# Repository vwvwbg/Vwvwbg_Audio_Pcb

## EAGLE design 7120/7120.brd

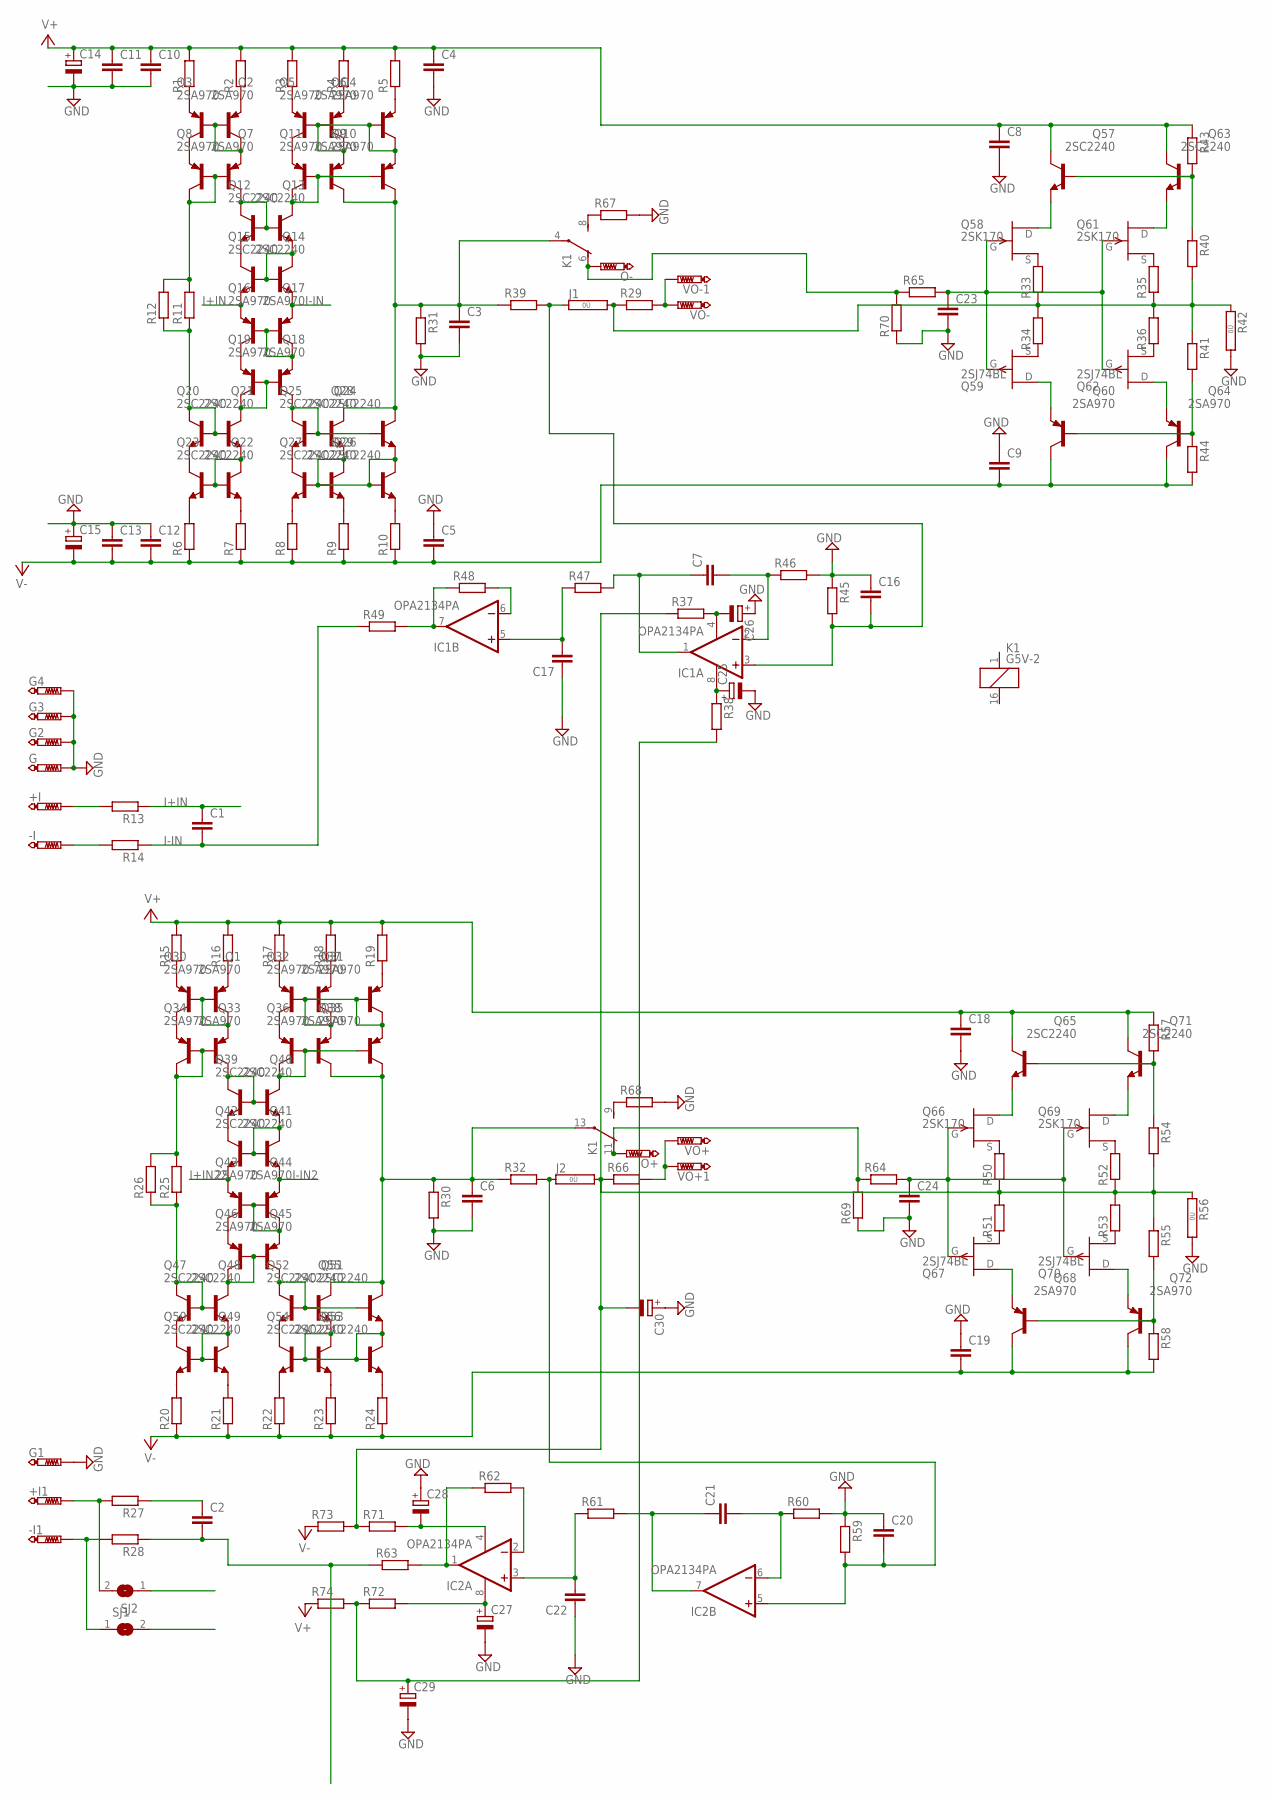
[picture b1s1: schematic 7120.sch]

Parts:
+I, +I1: PTR1PAD1-20; P1-20
-I, -I1: PTR1PAD1-20; P1-20
C1, C2, C7, C17, C21, C22: C-EU050-030X075; C050-030X075
C3, C4, C5, C6, C8, C9, C10, C11, C12, C13, C16, C18, C19, C20, C23, C24: C-EU050-055X075; C050-055X075
C14, C15, C29, C30: CPOL-EUE7.5-18; E7,5-18
C25, C26, C27, C28: CPOL-EUE2.5-6; E2,5-6
G, G1, G2, G3, G4: PTR1PAD1-20; P1-20
IC1, IC2: OPA2134PA; DIL08
J1, J2: 0R; 0R/10
K1: G5V-2
O+: PTR1PAD1-20; P1-20
O-: PTR1PAD1-20; P1-20
Q1, Q2, Q3, Q4, Q5, Q6, Q7, Q8, Q9, Q10, Q11, Q16, Q17, Q18, Q19, Q30, Q31, Q32, Q33, Q34, Q35, Q36, Q37, Q38, Q43, Q44, Q45, Q46, Q60, Q64, Q68, Q72: 2SA970; TO92-BCE
Q12, Q13, Q14, Q15, Q20, Q21, Q22, Q23, Q24, Q25, Q26, Q27, Q28, Q29, Q39, Q40, Q41, Q42, Q47, Q48, Q49, Q50, Q51, Q52, Q53, Q54, Q55, Q56, Q57, Q63, Q65, Q71: 2SC2240; TO92-BCE
Q58, Q61, Q66, Q69: 2SK170; TO92-
Q59, Q62, Q67, Q70: 2SJ74BL; TO92-
R1, R2, R3, R4, R5, R6, R7, R8, R9, R10, R11, R12, R13, R14, R15, R16, R17, R18, R19, R20, R21, R22, R23, R24, R25, R26, R27, R28, R29, R30, R31, R32, R33, R34, R35, R36, R37, R38, R39, R40, R41, R43, R44, R45, R46, R47, R48, R49, R50, R51, R52, R53, R54, R55, R57, R58, R59, R60, R61, R62, R63, R64, R65, R66, R67, R68, R69, R70, R71, R72, R73, R74: R-EU_0207/7; 0207/7
R42, R56: 0R; 0R/10
SJ1, SJ2: SJ
VO+, VO+1: PTR1PAD1-20; P1-20
VO-, VO-1: PTR1PAD1-20; P1-20

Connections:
+I: +I.TP, R13.2, SJ1.2
-I: -I.TP, R14.2, SJ2.1
GND: C3.2, C4.2, C5.1, C6.2, C8.2, C9.1, C10.2, C11.2, C12.1, C13.1, C14.-, C15.+, C16.1, C17.1, C18.2, C19.1, C20.1, C22.1, C23.2, C24.2, C25.-, C26.+, C27.-, C28.+, C29.-, C30.+, G.TP, G1.TP, G2.TP, G3.TP, G4.TP, R30.2, R31.2, R42.2, R45.1, R46.2, R56.2, R59.1, R60.2, R67.2, R68.2, R69.1, R70.1
I+IN: C1.1, Q14.E, Q17.E, R13.1
I+IN2: C2.1, R27.1
I+IN22: Q41.E, Q44.E
I-IN: C1.2, Q15.E, Q16.E, R14.1, R49.1
I-IN1: C2.2, R28.1, R63.1
I-IN2: Q42.E, Q43.E
unnamed: Q2.E, R1.1
unnamed: Q2.B, Q3.B, Q3.C, Q8.E
unnamed: Q3.E, R2.1
unnamed: Q2.C, Q7.E
unnamed: Q7.B, Q7.C, Q8.B, R11.2, R12.2
unnamed: Q4.E, R3.1
unnamed: Q4.B, Q5.B, Q5.C, Q6.B, Q6.C, Q9.E, Q11.E
unnamed: Q5.E, R4.1
unnamed: Q6.E, R5.1
unnamed: Q8.C, Q12.B, Q13.B, Q13.C
unnamed: C3.1, K1.4, Q9.C, Q11.C, Q25.C, Q28.C, R31.1, R39.1
unnamed: Q4.C, Q10.E
unnamed: Q12.E, Q14.B, Q15.B, Q15.C
unnamed: Q9.B, Q10.B, Q10.C, Q11.B, Q12.C
unnamed: C16.2, IC1.3 (+IN), J1.1, R39.2, R45.2
unnamed: Q13.E, Q14.C
unnamed: C6.1, K1.13, Q36.C, Q38.C, Q52.C, Q55.C, R30.1, R32.1
unnamed: Q57.B, Q63.B, R40.1, R43.2
unnamed: Q1.E, R15.1
unnamed: Q16.B, Q16.C, Q17.B, Q19.E
unnamed: Q17.C, Q18.E
unnamed: Q1.B, Q30.B, Q30.C, Q34.E
unnamed: Q18.B, Q18.C, Q19.B, Q20.C
unnamed: Q30.E, R16.1
unnamed: Q20.B, Q21.B, Q21.C, R11.1, R12.1
unnamed: Q21.E, Q22.C
unnamed: Q20.E, Q22.B, Q23.B, Q23.C
unnamed: Q33.B, Q33.C, Q34.B, R25.2, R26.2
unnamed: Q19.C, Q24.B, Q24.C, Q25.B, Q28.B
unnamed: Q1.C, Q33.E
unnamed: Q24.E, Q26.C
unnamed: Q25.E, Q26.B, Q27.B, Q27.C, Q28.E, Q29.B, Q29.C
unnamed: Q31.E, R17.1
unnamed: Q31.B, Q32.B, Q32.C, Q36.E, Q37.B, Q37.C, Q38.E
unnamed: Q32.E, R18.1
unnamed: Q22.E, R6.2
unnamed: Q23.E, R7.2
unnamed: Q26.E, R8.2
unnamed: Q27.E, R9.2
unnamed: Q29.E, R10.2
unnamed: J1.2, R29.1, R33.1, R34.2, R35.1, R36.2, R40.2, R41.1, R42.1
unnamed: Q31.C, Q35.E
unnamed: Q35.B, Q35.C, Q36.B, Q38.B, Q39.C
unnamed: K1.6 (O), O-.TP, R65.1, R70.2
unnamed: Q37.E, R19.1
unnamed: Q60.B, Q64.B, R41.2, R44.1
unnamed: Q34.C, Q39.B, Q40.B, Q40.C
unnamed: Q40.E, Q41.C
unnamed: Q39.E, Q41.B, Q42.B, Q42.C
unnamed: Q43.B, Q43.C, Q44.B, Q46.E
unnamed: Q44.C, Q45.E
unnamed: Q45.B, Q45.C, Q46.B, Q47.C
unnamed: Q47.B, Q48.B, Q48.C, R25.1, R26.1
unnamed: Q48.E, Q49.C
unnamed: Q47.E, Q49.B, Q50.B, Q50.C
unnamed: Q46.C, Q51.B, Q51.C, Q52.B, Q55.B
unnamed: Q51.E, Q53.C
unnamed: Q49.E, R20.2
unnamed: Q50.E, R21.2
unnamed: Q53.E, R22.2
unnamed: Q54.E, R23.2
unnamed: Q56.E, R24.2
unnamed: C7.1, IC1.1 (OUT), R47.2
unnamed: Q52.E, Q53.B, Q54.B, Q54.C, Q55.E, Q56.B, Q56.C
unnamed: +I1.TP, R27.2, SJ2.2
unnamed: -I1.TP, R28.2, SJ1.1
unnamed: Q62.3 (S), R36.1
unnamed: Q59.3 (S), R34.1
unnamed: K1.8 (S), R67.1
unnamed: Q58.3 (S), R33.2
unnamed: Q61.3 (S), R35.2
unnamed: C7.2, IC1.2 (-IN), R46.1
unnamed: C23.1, Q58.2 (G), Q59.2 (G), Q61.2 (G), Q62.2 (G), R65.2
unnamed: Q61.1 (D), Q63.E
unnamed: C17.2, IC1.5 (+IN), R47.1
unnamed: Q57.E, Q58.1 (D)
unnamed: Q62.1 (D), Q64.E
unnamed: Q59.1 (D), Q60.E
unnamed: IC1.7 (OUT), R48.1, R49.2
unnamed: IC1.6 (-IN), R48.2
unnamed: Q65.B, Q71.B, R54.1, R57.2
unnamed: Q68.B, Q72.B, R55.2, R58.1
unnamed: J2.2, R50.1, R51.2, R52.1, R53.2, R54.2, R55.1, R56.1, R66.1
unnamed: C24.1, Q66.2 (G), Q67.2 (G), Q69.2 (G), Q70.2 (G), R64.2
unnamed: Q70.3 (S), R53.1
unnamed: Q67.3 (S), R51.1
unnamed: Q69.1 (D), Q71.E
unnamed: Q70.1 (D), Q72.E
unnamed: Q67.1 (D), Q68.E
unnamed: Q69.3 (S), R52.2
unnamed: Q66.3 (S), R50.2
unnamed: Q65.E, Q66.1 (D)
unnamed: C21.1, IC2.7 (OUT), R61.2
unnamed: C21.2, IC2.6 (-IN), R60.1
unnamed: C20.2, IC2.5 (+IN), J2.1, R32.2, R59.2
unnamed: K1.9 (S), R68.1
unnamed: C22.2, IC2.3 (+IN), R61.1
unnamed: IC2.1 (OUT), R62.1, R63.2
unnamed: IC2.2 (-IN), R62.2
unnamed: R66.2, VO+.TP, VO+1.TP
unnamed: K1.11 (O), O+.TP, R64.1, R69.2
unnamed: R29.2, VO-.TP, VO-1.TP
unnamed: C28.-, IC2.4 (V-), R71.2
unnamed: C27.+, IC2.8 (V+), R72.2
unnamed: C25.+, IC1.8 (V+), R38.1
unnamed: C26.-, IC1.4 (V-), R37.2
unnamed: C30.-, R37.1, R71.1, R73.2
unnamed: C29.+, R38.2, R72.1, R74.2
V+: C4.1, C8.1, C10.1, C11.1, C14.+, C18.1, Q57.C, Q63.C, Q65.C, Q71.C, R1.2, R2.2, R3.2, R4.2, R5.2, R15.2, R16.2, R17.2, R18.2, R19.2, R43.1, R57.1, R74.1
V-: C5.2, C9.2, C12.2, C13.2, C15.-, C19.2, Q60.C, Q64.C, Q68.C, Q72.C, R6.1, R7.1, R8.1, R9.1, R10.1, R20.1, R21.1, R22.1, R23.1, R24.1, R44.2, R58.2, R73.1

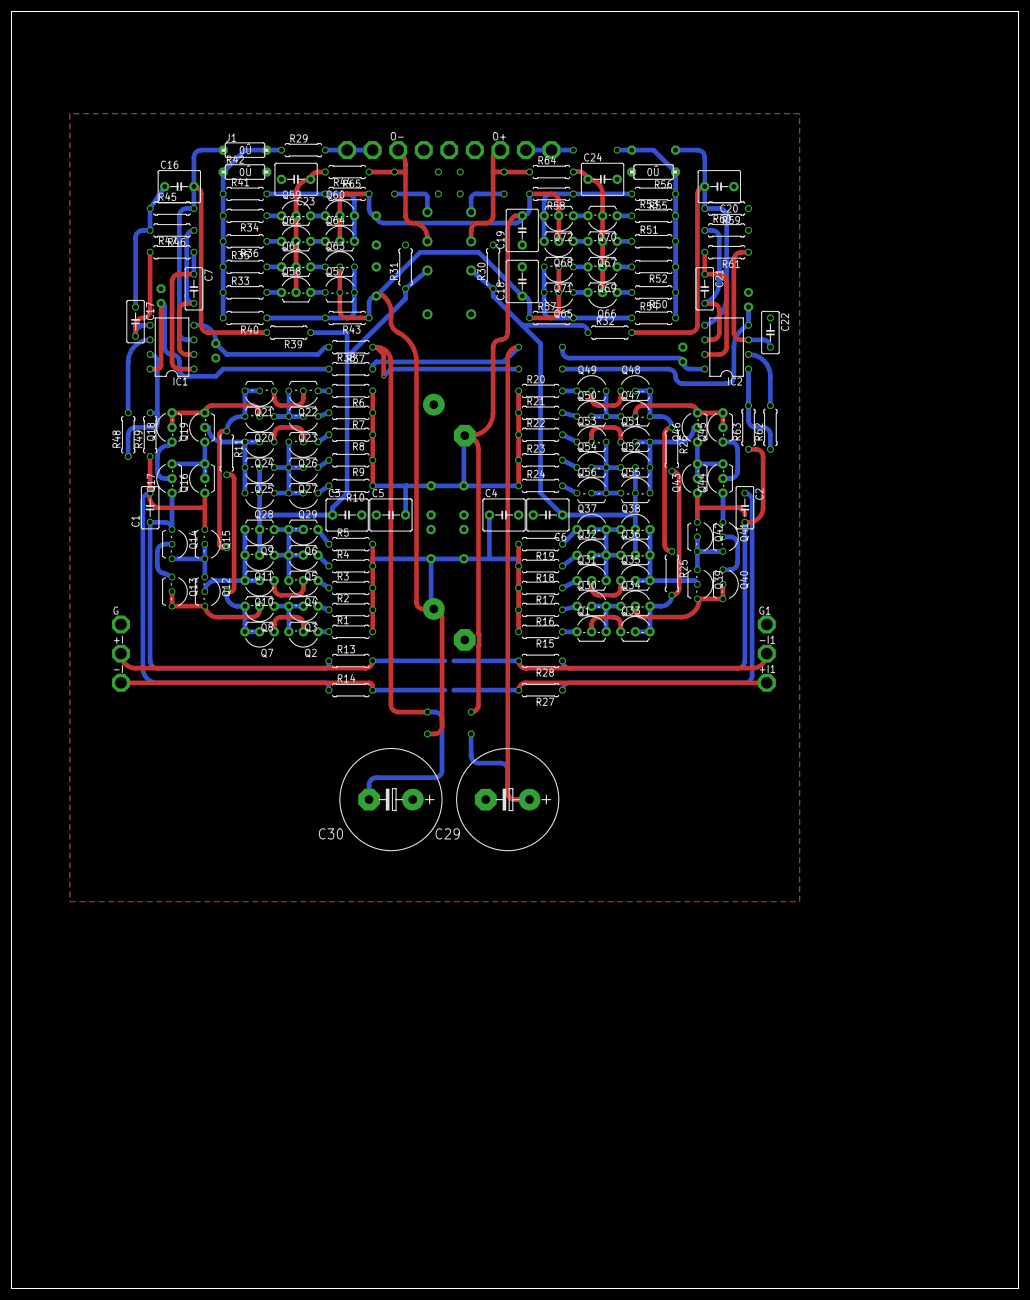
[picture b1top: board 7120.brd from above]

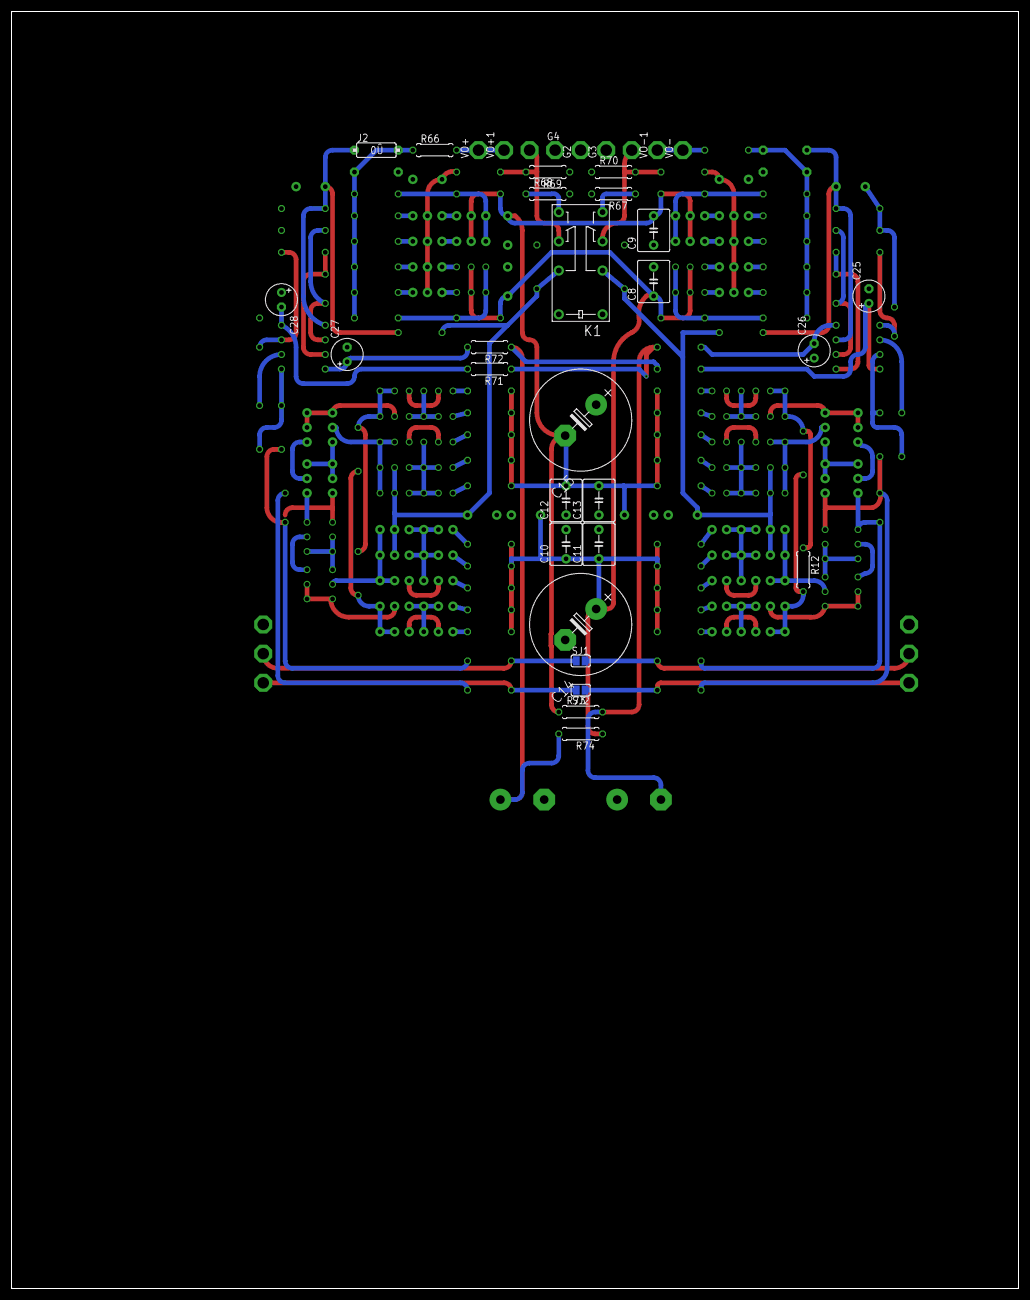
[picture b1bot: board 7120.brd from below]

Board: 2 copper layers, 175.3 x 222.2 mm, 198 parts (33 on the bottom side), 119 nets.

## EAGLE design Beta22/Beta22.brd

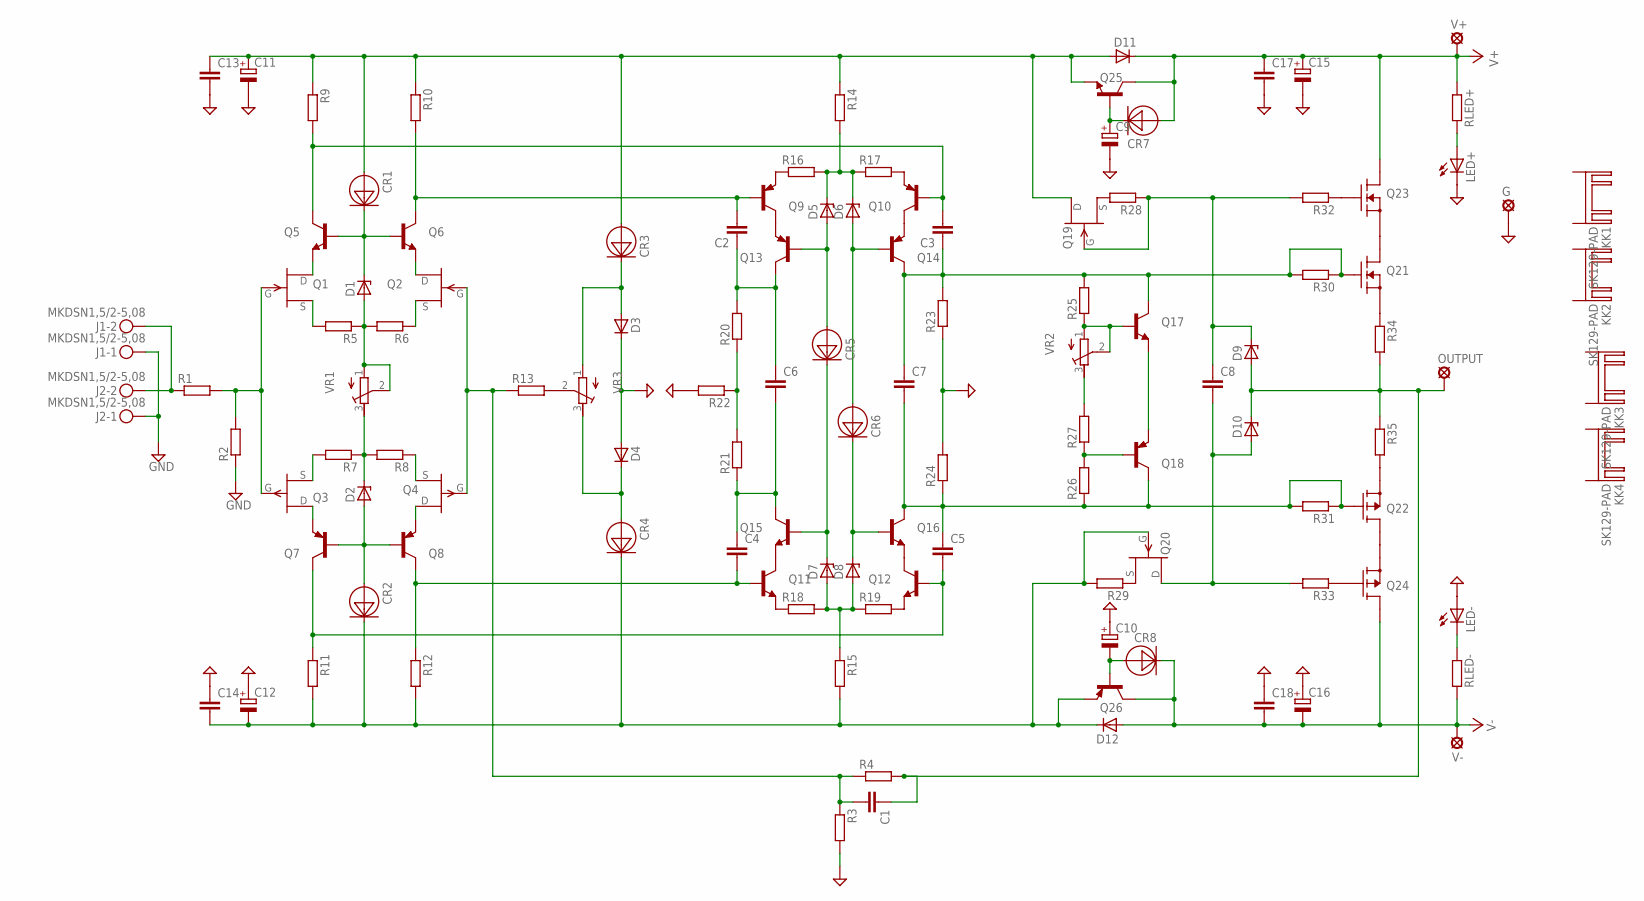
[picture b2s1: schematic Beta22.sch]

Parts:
C1, C2, C3, C4, C5: C-EU025_050-025X075; C025_050-025X075
C6, C7, C8, C13, C14, C17, C18: C-EU050-055X075; C050-055X075
C9, C10, C11, C12: CPOL-EUE5-13; E5-13
C15, C16: CPOL-EUE7.5-18; E7,5-18
CR1, CR2, CR3, CR4, CR5, CR6, CR7, CR8: E-202; DO-35-3
D1, D2, D5, D6, D7, D8, D9, D10: BZV10; DO34Z7
D3, D4, D11, D12: 1N4148-V; 1N4148
G: SE14
J1, J2: MKDSN1,5/2-5,08
KK1, KK2, KK3, KK4: SK129-PAD; SK129
LED+: LED5MM
LED-: LED5MM
OUTPUT: SE14
Q1, Q2: 2SK170; TO92-
Q3, Q4: 2SJ74BL; TO92-
Q5, Q6, Q11, Q12, Q15, Q16, Q17, Q25: BC550; TO92-EBC
Q7, Q8, Q9, Q10, Q13, Q14, Q18, Q26: BC560; TO92_1
Q19, Q20: PN4392; TO92-
Q21, Q23: IRFZ24N; TO220V
Q22, Q24: IRFZ34N; TO220V
R1, R2, R3, R4, R5, R6, R7, R8, R9, R10, R11, R12, R13, R14, R15, R16, R17, R18, R19, R20, R21, R22, R23, R24, R25, R26, R27, R28, R29, R30, R31, R32, R33: R-EU_0309/10; 0309/10
R34, R35: R-EU_0617/17; 0617/17
RLED+: R-EU_0309/10; 0309/10
RLED-: R-EU_0309/10; 0309/10
V+: SE14
V-: SE14
VR1, VR2, VR3: R-TRIMM3296W; RTRIM3296W

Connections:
GND: C9.-, C10.+, C11.-, C12.+, C13.2, C14.1, C15.-, C16.+, C17.2, C18.1, D3.C, D4.A, G.MP, J1.1, J2.1, LED+.K (C), LED-.A, R2.1, R3.2, R22.2, R23.1, R24.2
unnamed: Q1.2 (G), Q3.2 (G), R1.2, R2.2
unnamed: Q2.1 (D), Q6.E
unnamed: Q1.3 (S), R5.2
unnamed: Q3.3 (S), R7.2
unnamed: Q1.1 (D), Q5.E
unnamed: Q3.1 (D), Q7.3 (E)
unnamed: Q2.3 (S), R6.1
unnamed: D2.C, R7.1, R8.2, VR1.3 (E)
unnamed: Q4.3 (S), R8.1
unnamed: Q4.1 (D), Q8.3 (E)
unnamed: D1.A, R5.1, R6.2, VR1.1 (A), VR1.2 (S)
unnamed: CR2.ANODE, D2.A, Q7.2 (B), Q8.2 (B)
unnamed: C3.2, C3.3 (2), Q5.C, Q10.2 (B), R9.2
unnamed: C2.2, C2.3 (2), Q6.C, Q9.2 (B), R10.2
unnamed: CR4.ANODE, D4.C, VR3.3 (E)
unnamed: CR1.1 (CATHODE), CR1.2 (CATHODE), CR1.CATHODE, D1.C, Q5.B, Q6.B
unnamed: C12.-, C14.2, CR2.1 (CATHODE), CR2.2 (CATHODE), CR2.CATHODE, CR4.1 (CATHODE), CR4.2 (CATHODE), CR4.CATHODE, D12.C, Q20.1 (G), Q26.3 (E), R11.2, R12.2, R15.2, R29.2
unnamed: C5.2, C5.3 (2), Q7.1 (C), Q12.B, R11.1
unnamed: J1.2, J2.2, R1.1
unnamed: C8.2, D10.A, Q20.3 (D), R33.2
unnamed: C1.2, C1.3 (2), Q2.2 (G), Q4.2 (G), R3.1, R4.1, R13.1
unnamed: R13.2, VR3.2 (S)
unnamed: Q9.1 (C), Q13.3 (E)
unnamed: CR3.1 (CATHODE), CR3.2 (CATHODE), CR3.CATHODE, D3.A, VR3.1 (A)
unnamed: Q10.1 (C), Q14.3 (E)
unnamed: C1.1, D9.A, D10.C, OUTPUT.MP, R4.2, R34.2, R35.1
unnamed: Q9.3 (E), R16.1
unnamed: Q10.3 (E), R17.2
unnamed: D5.C, D6.C, R14.2, R16.2, R17.1
unnamed: Q11.E, R18.1
unnamed: Q12.E, R19.2
unnamed: D7.A, D8.A, R15.1, R18.2, R19.1
unnamed: C4.2, C4.3 (2), Q8.1 (C), Q11.B, R12.1
unnamed: R20.1, R21.2, R22.1
unnamed: C2.1, C6.1, Q13.1 (C), R20.2
unnamed: C4.1, C6.2, Q15.C, R21.1
unnamed: Q11.C, Q15.E
unnamed: Q12.C, Q16.E
unnamed: Q17.B, R25.1, VR2.1 (A), VR2.2 (S)
unnamed: Q19.2 (S), R28.2
unnamed: Q20.2 (S), R29.1
unnamed: C3.1, C7.1, Q14.1 (C), Q17.C, Q21.1 (G), R23.2, R25.2, R30.1, R30.2
unnamed: CR5.ANODE, D5.A, Q13.2 (B)
unnamed: CR6.ANODE, D6.A, Q14.2 (B)
unnamed: CR5.1 (CATHODE), CR5.2 (CATHODE), CR5.CATHODE, D7.C, Q15.B
unnamed: CR6.1 (CATHODE), CR6.2 (CATHODE), CR6.CATHODE, D8.C, Q16.B
unnamed: Q18.2 (B), R26.2, R27.1
unnamed: R27.2, VR2.3 (E)
unnamed: Q17.E, Q18.3 (E)
unnamed: C5.1, C7.2, Q16.C, Q18.1 (C), Q22.1 (G), R24.1, R26.1, R31.1, R31.2
unnamed: C11.+, C13.1, CR1.ANODE, CR3.ANODE, D11.A, Q19.3 (D), Q25.E, R9.1, R10.1, R14.1
unnamed: C10.-, CR8.ANODE, Q26.2 (B)
unnamed: C8.1, D9.C, Q19.1 (G), R28.1, R32.2
unnamed: Q21.2 (D), Q23.3 (S)
unnamed: Q22.2 (D), Q24.3 (S)
unnamed: Q23.1 (G), R32.1
unnamed: Q24.1 (G), R33.1
unnamed: LED+.A, RLED+.2
unnamed: Q21.3 (S), R34.1
unnamed: Q22.3 (S), R35.2
unnamed: C9.+, CR7.1 (CATHODE), CR7.2 (CATHODE), CR7.CATHODE, Q25.B
unnamed: LED-.K (C), RLED-.1
V+: C15.+, C17.1, CR7.ANODE, D11.C, Q23.2 (D), Q25.C, RLED+.1, V+.MP
V-: C16.-, C18.2, CR8.1 (CATHODE), CR8.2 (CATHODE), CR8.CATHODE, D12.A, Q24.2 (D), Q26.1 (C), RLED-.2, V-.MP

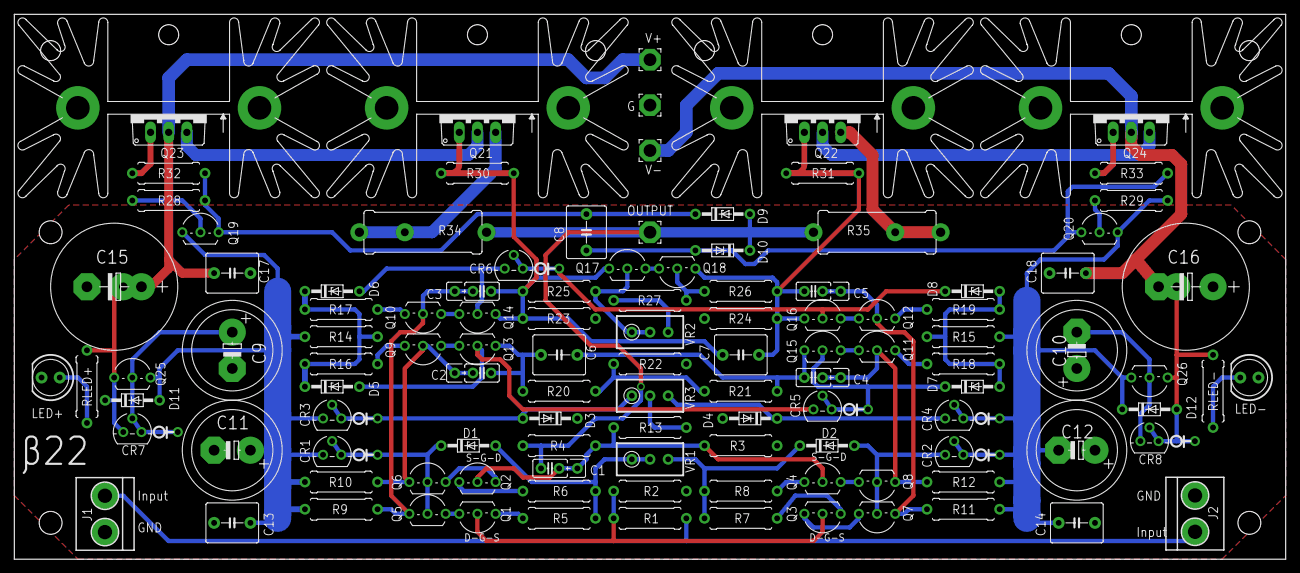
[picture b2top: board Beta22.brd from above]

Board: 2 copper layers, 177.8 x 76.2 mm, 116 parts (0 on the bottom side), 65 nets.

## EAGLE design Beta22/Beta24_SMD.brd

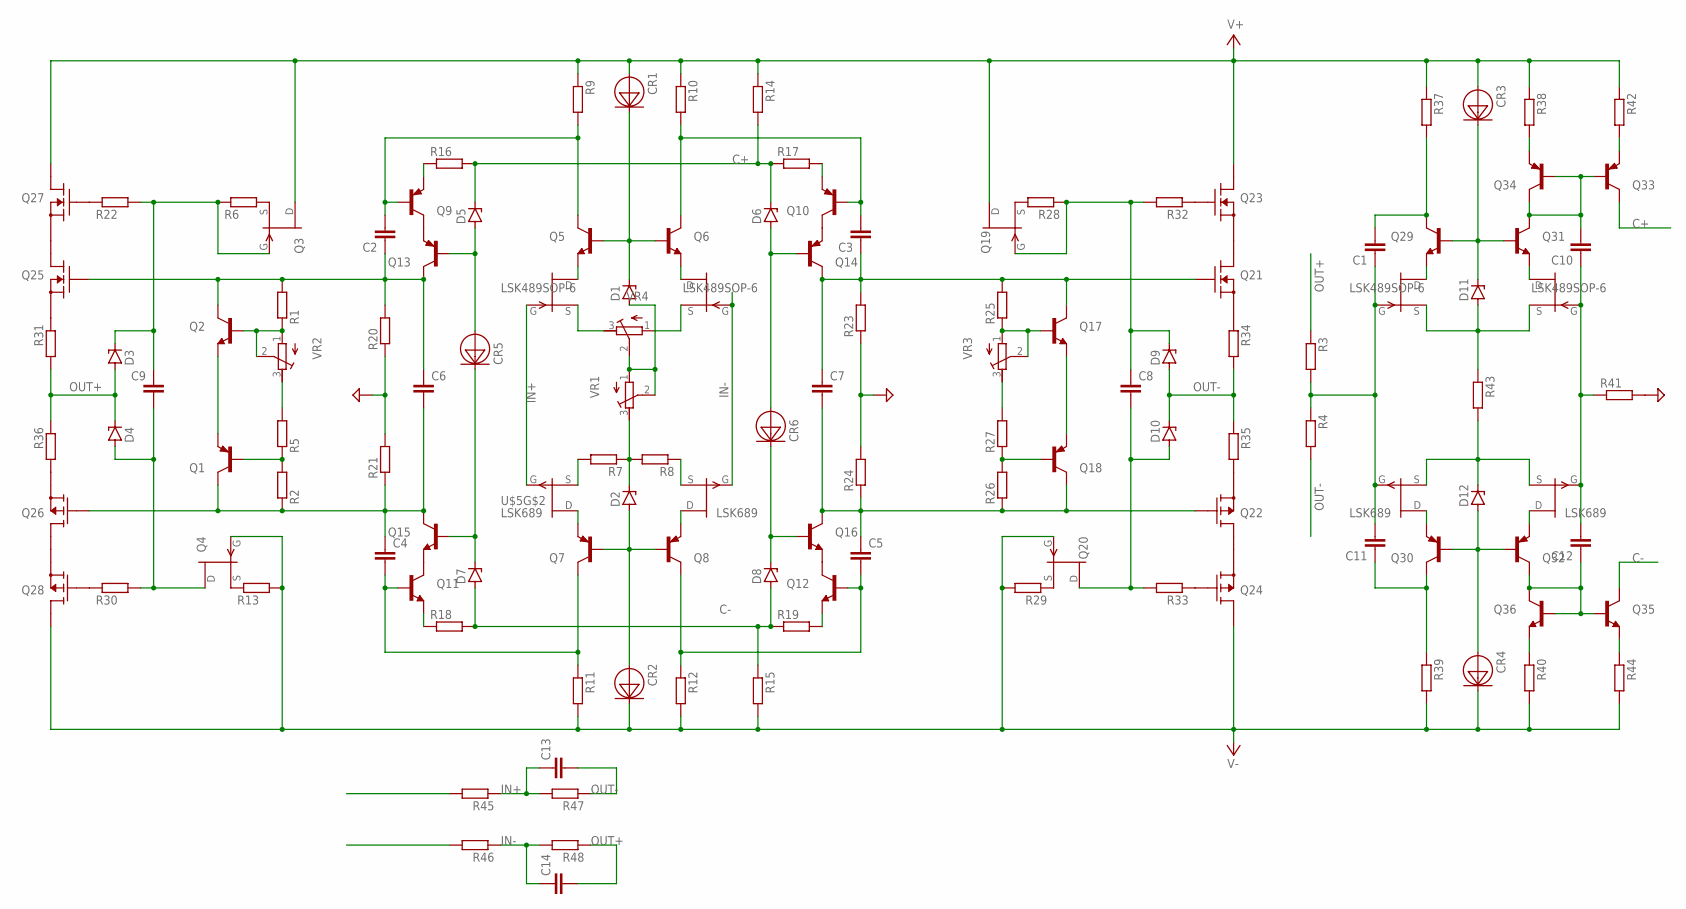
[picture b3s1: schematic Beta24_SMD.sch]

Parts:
C1, C2, C3, C4, C5, C6, C7, C8, C9, C10, C11, C12, C13, C14: C-EUC1206; C1206
CR1, CR2, CR3, CR4, CR5, CR6: 1N5283; SMD
D1, D2, D3, D4, D5, D6, D7, D8, D9, D10, D11, D12: ZENER-DIODESOD80C; SOD80C
Q1, Q7, Q8, Q9, Q10, Q13, Q14, Q18, Q30, Q32, Q33, Q34: TRANSISTOR_BC858C-PNP-SOT23-BEC; TRANSISTOR_SOT23-BEC
Q2, Q5, Q6, Q11, Q12, Q15, Q16, Q17, Q29, Q31, Q35, Q36: TRANSISTOR_BC850-NPN-SOT23-BEC; TRANSISTOR_SOT23-BEC
Q3, Q4, Q19, Q20: SST5486; SOT23
Q21, Q23, Q25, Q27: IRFZ24N; TO220V
Q22, Q24, Q26, Q28: IRFZ34N; TO220V
R1, R2, R3, R4, R5, R6, R7, R8, R9, R10, R11, R12, R13, R14, R15, R16, R17, R18, R19, R20, R21, R22, R23, R24, R25, R26, R27, R28, R29, R30, R32, R33, R37, R38, R39, R40, R41, R42, R43, R44, R45, R46, R47, R48: R-EU_MELF0204W; MINI_MELF-0204W
R31, R34, R35, R36: R-EU_0617/17; 0617/17
U$1, U$3: LSK489SOP-6; SOT-23-6
U$4, U$5: LSK689; SOT-23-6
VR1, VR2, VR3, VR4: R-TRIMM3296W; RTRIM3296W

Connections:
C+: D5.C, D6.C, Q33.C, R14.2, R16.2, R17.1
C-: D7.A, D8.A, Q35.C, R15.1, R18.2, R19.1
GND: R20.1, R21.2, R23.1, R24.2, R41.2
IN+: C13.1, R45.1, R47.2, U$1.1 (G), U$5.4 (G)
IN-: C14.1, R46.1, R48.2, U$1.4 (G), U$5.1 (G)
unnamed: C12.1, Q32.C, Q35.B, Q36.B, Q36.C
unnamed: Q6.E, U$1.5 (D)
unnamed: U$1.3 (S), VR4.3 (E)
unnamed: R7.2, U$5.6 (S)
unnamed: Q5.E, U$1.2 (D)
unnamed: Q7.E, U$5.5 (D)
unnamed: U$1.6 (S), VR4.1 (A)
unnamed: D2.C, R7.1, R8.2, VR1.3 (E)
unnamed: R8.1, U$5.3 (S)
unnamed: Q8.E, U$5.2 (D)
unnamed: D1.A, VR1.1 (A), VR1.2 (S), VR4.2 (S)
unnamed: CR2.ANODE, D2.A, Q7.B, Q8.B
unnamed: C2.2, Q5.C, Q9.B, R9.2
unnamed: C3.2, Q6.C, Q10.B, R10.2
unnamed: C3.1, C7.1, Q14.C, Q17.C, Q21.1 (G), R23.2, R25.2
unnamed: CR1.CATHODE, D1.C, Q5.B, Q6.B
unnamed: Q36.E, R40.1
unnamed: C5.2, Q8.C, Q12.B, R12.1
unnamed: C1.1, C11.2, R3.2, R4.1, U$3.1 (G), U$4.1 (G)
unnamed: C8.2, D10.A, Q20.1 (D), R33.2
unnamed: D12.C, R43.2, U$4.3 (S), U$4.6 (S)
unnamed: D11.A, R43.1, U$3.3 (S), U$3.6 (S)
unnamed: Q9.C, Q13.E
unnamed: C4.2, Q7.C, Q11.B, R11.1
unnamed: Q10.C, Q14.E
unnamed: Q34.E, R38.2
unnamed: Q9.E, R16.1
unnamed: Q10.E, R17.2
unnamed: C10.2, Q31.C, Q33.B, Q34.B, Q34.C
unnamed: Q11.E, R18.1
unnamed: Q12.E, R19.2
unnamed: Q31.E, U$3.5 (D)
unnamed: CR4.ANODE, D12.A, Q30.B, Q32.B
unnamed: C2.1, C6.1, Q2.C, Q13.C, Q25.1 (G), R1.2, R20.2
unnamed: C4.1, C6.2, Q1.C, Q15.C, Q26.1 (G), R2.1, R21.1
unnamed: Q11.C, Q15.E
unnamed: Q12.C, Q16.E
unnamed: Q17.B, R25.1, VR3.1 (A), VR3.2 (S)
unnamed: Q19.2 (S), R28.2
unnamed: Q20.2 (S), R29.1
unnamed: C1.2, Q29.C, R37.2
unnamed: CR5.ANODE, D5.A, Q13.B
unnamed: CR6.ANODE, D6.A, Q14.B
unnamed: CR5.CATHODE, D7.C, Q15.B
unnamed: CR6.CATHODE, D8.C, Q16.B
unnamed: Q18.B, R26.2, R27.1
unnamed: R27.2, VR3.3 (E)
unnamed: Q17.E, Q18.E
unnamed: C5.1, C7.2, Q16.C, Q18.C, Q22.1 (G), R24.1, R26.1
unnamed: Q1.B, R2.2, R5.1
unnamed: Q1.E, Q2.E
unnamed: Q35.E, R44.1
unnamed: C8.1, D9.C, Q19.3 (G), R28.1, R32.2
unnamed: Q3.2 (S), R6.2
unnamed: Q4.2 (S), R13.1
unnamed: Q21.2 (D), Q23.3 (S)
unnamed: Q22.2 (D), Q24.3 (S)
unnamed: Q23.1 (G), R32.1
unnamed: Q24.1 (G), R33.1
unnamed: C9.1, D3.C, Q3.3 (G), R6.1, R22.2
unnamed: Q21.3 (S), R34.1
unnamed: Q22.3 (S), R35.2
unnamed: C9.2, D4.A, Q4.1 (D), R30.2
unnamed: Q25.2 (D), Q27.3 (S)
unnamed: Q26.2 (D), Q28.3 (S)
unnamed: Q27.1 (G), R22.1
unnamed: Q28.1 (G), R30.1
unnamed: Q25.3 (S), R31.1
unnamed: Q26.3 (S), R36.2
unnamed: Q2.B, R1.1, VR2.1 (A), VR2.2 (S)
unnamed: R5.2, VR2.3 (E)
unnamed: CR3.CATHODE, D11.C, Q29.B, Q31.B
unnamed: Q29.E, U$3.2 (D)
unnamed: C10.1, C12.2, R41.1, U$3.4 (G), U$4.4 (G)
unnamed: Q30.E, U$4.2 (D)
unnamed: Q32.E, U$4.5 (D)
unnamed: C11.1, Q30.C, R39.1
unnamed: Q33.E, R42.2
OUT+: C14.2, D3.A, D4.C, R3.1, R31.2, R36.1, R48.1
OUT-: C13.2, D9.A, D10.C, R4.2, R34.2, R35.1, R47.1
V+: CR1.ANODE, CR3.ANODE, Q3.1 (D), Q19.1 (D), Q23.2 (D), Q27.2 (D), R9.1, R10.1, R14.1, R37.1, R38.1, R42.1
V-: CR2.CATHODE, CR4.CATHODE, Q4.3 (G), Q20.3 (G), Q24.2 (D), Q28.2 (D), R11.2, R12.2, R13.2, R15.2, R29.2, R39.2, R40.2, R44.2

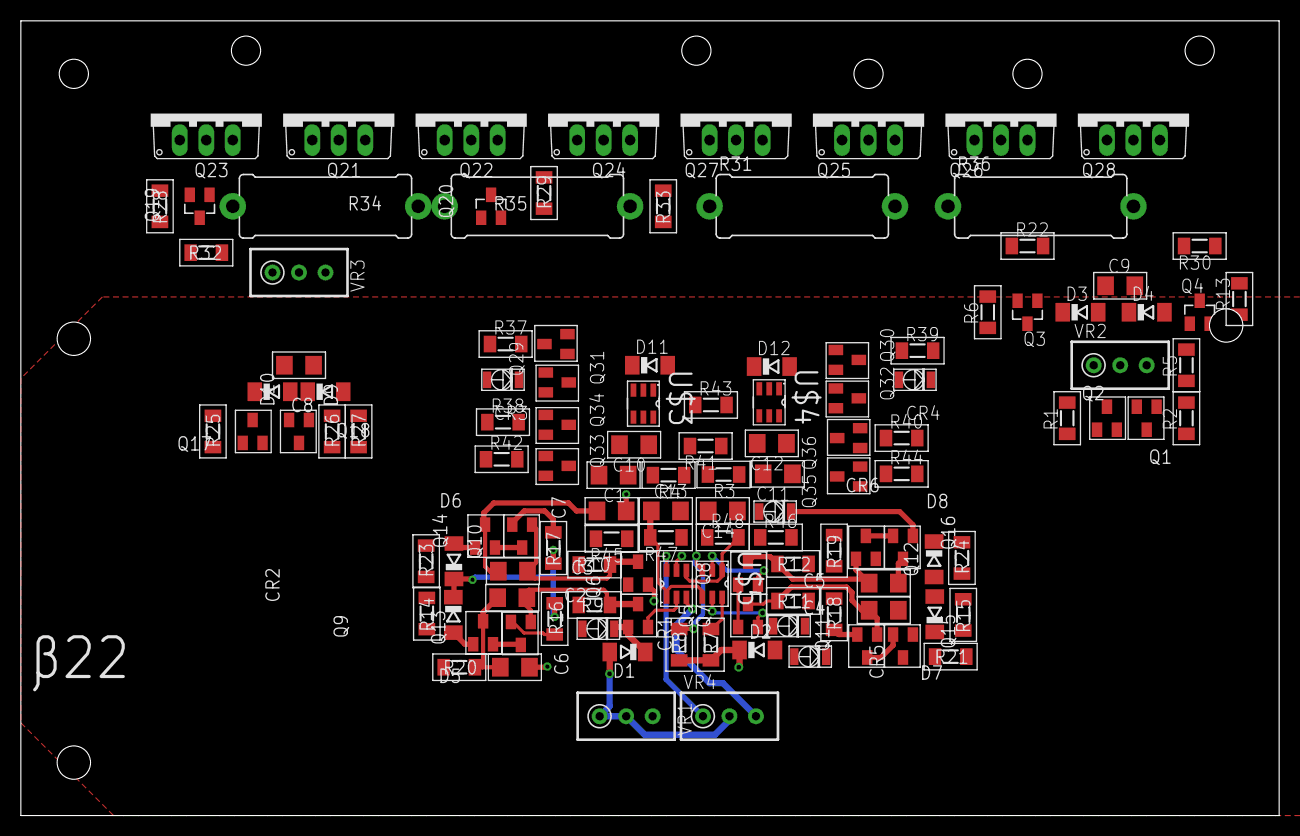
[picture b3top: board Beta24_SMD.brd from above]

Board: 4 copper layers, 120.7 x 76.2 mm, 124 parts (0 on the bottom side), 87 nets.
